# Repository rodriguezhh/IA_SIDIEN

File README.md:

# DIAGNÓSTICO DE ENFERMEDADES EN LA HOJA DEL TOMATE MEDIANTE UN SISTEMA EMBEBIDO USANDO INTELIGENCIA ARTIFICIAL E IMÁGENES.

## Descripción del sistema

Este proyecto tiene como objetivo diseñar e implementar un algoritmo de aprendizaje profundo que permita identificar enfermedades en la hoja de la planta del tomate desplegado en un sistema embebido. El sistema está destinado para servir como herramient a agricultores experimentados como a ingenieros agrónomos, con el objetivo de realizar diagnósticos tempranos y asegurar la salud del cultivo.Además, la implementación de este sistema también puede tener fines educativos, permitiendo el estudio de las enfermedades que afectan a las hojas de tomate y apoyando el seguimiento de los cultivos.

Para llevar a cabo este proyecto, se utilizó una base de datos proporcionada por la comunidad Kaggle. Además, se visitaron diferentes invernaderos para capturar imágenes de hojas sanas y enfermas de los cultivos de tomate. Se emplearon herramientas de software libre y código abierto para cada etapa del proyecto.

Se entrenó una inteligencia artificial de jerarquía simplificada y tres modelos de Transfer Learning utilizando Google Colaboratory.

Finalmente, el modelo resultante fue implementado en dos sistemas embebidos, NVIDIA Jetson Nano de 4GB y Raspberry pi 4B. Se realizó un análisis comparativo de los resultados obtenidos para validar su rendimiento en ambas tarjetas de desarrollo.

## Video sobre el desarrollo del proyecto.
https://youtu.be/ES93pp3hpe4

## Drive del proyecto.
https://drive.google.com/drive/folders/18Io3CUIHZYFtg3d0LMKD3wjqCA_87UzG?usp=sharing

## Manual de Usuario 
### Paso a paso del Hardware
1. Accione el interruptor para encender el dispositivo TOLD2.

2. Si va a hacer uso del porta muestras, accione el interruptor para encender la luz del dispositivo TOLD2.

3. Seleccione la muestra de hoja de la plante del tomate que desea inspeccionar y asegurela con el alfiler en el porta muestras y depositela.

5. Diríjase al apartado ’Paso a paso de la interfaz de usuario’ para proceder con el diagnóstico.

 ### NOTA: 
 En caso de que el dispositivo TOLD2 no encienda, conecte el cargador en el puerto al costado del dispositivo TOLD2. 

### Paso a paso de la Interfaz de usuario 
1. Al iniciar el dispositivo, debe observar la siguiente pantalla.

2. Haga doble click sobre el icono "hacer detección". Acontinuación se debe abrir una interfaz como la siguiente. Asegurese de abrir el software unicamente con dos clicks, de lo contrario se abrirá más de una ventana.

3. Captue la imagen haciendo click en el boton "Tomar foto". 
4. Haga click en el botón "hacer detección". 
5. Finalemte podra observar un diagnóstico de su hoja, además. Si desea realizar otra predicción puede hacer click sobre ”Nueva detección" y repita el proceso cuantas veces desee.

## Contribución
Este proyecto se encuentra en constante evolución, por lo que cualquier contribución será bienvenida. Si deseas contribuir, por favor envía un pull request o contacta al equipo de desarrollo.

## Contacto 
* Camilo Andres Santos Ortiz. camilosantos6584@gmail.com
* Harold Hernando Rodriguez Rodriguez. rodriguezhh03@gmail.com
* Wilmer Andres Guerrero Rangel. andresguerrero1204@gmail.com

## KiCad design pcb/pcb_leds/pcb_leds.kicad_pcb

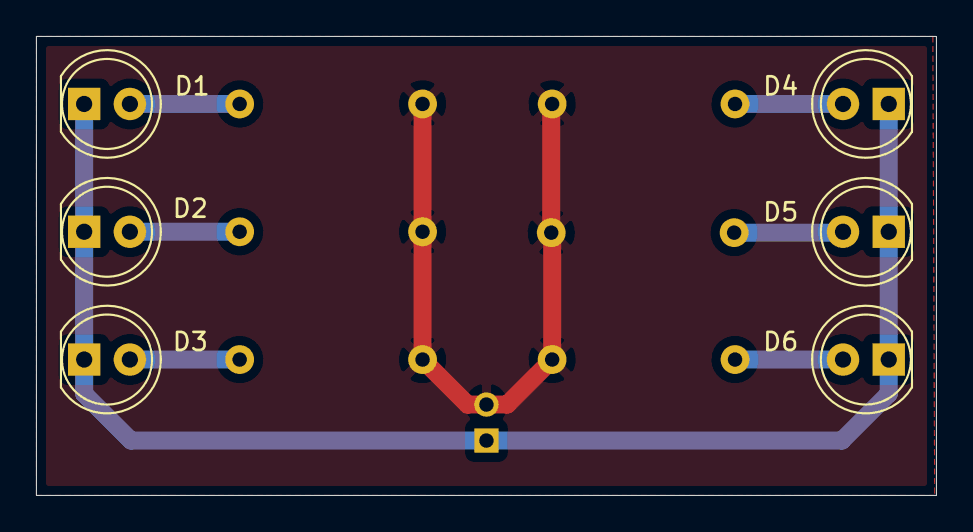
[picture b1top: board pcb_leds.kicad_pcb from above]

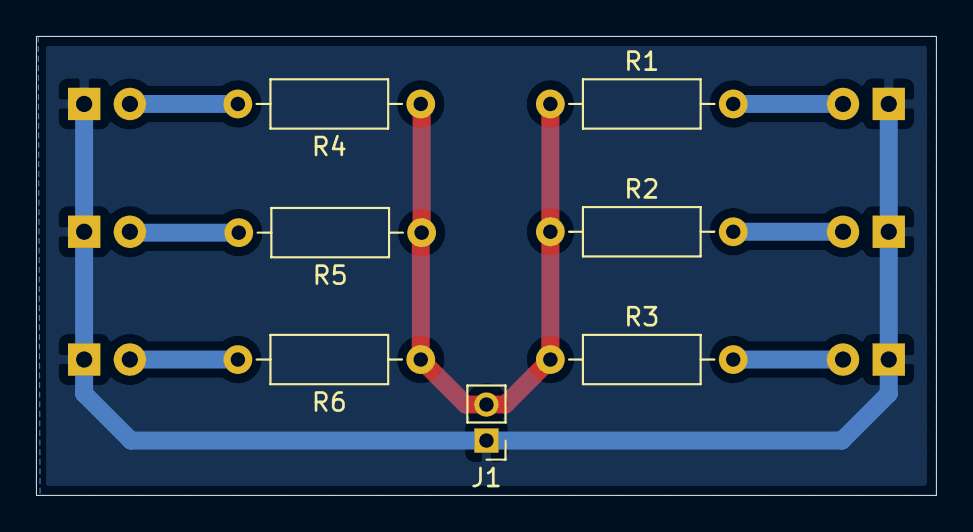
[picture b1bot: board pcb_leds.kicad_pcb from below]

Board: 2 copper layers, 50.0 x 25.5 mm, 13 parts (7 on the bottom side), 8 nets.

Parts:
D1, D2, D3, D4, D5, D6: LED; LED_D5.0mm
J1: Screw_Terminal_01x02; PinHeader_1x02_P2.00mm_Vertical
R1, R2, R3, R4, R5, R6: 160; R_Axial_DIN0207_L6.3mm_D2.5mm_P10.16mm_Horizontal

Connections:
+5V: J1.2, R1.1, R2.1, R3.1, R4.1, R5.1, R6.1
GND: D1.1, D2.1, D3.1, D4.1, D5.1, D6.1, J1.1
unnamed: D1.2, R1.2
unnamed: D2.2, R2.2
unnamed: D3.2, R3.2
unnamed: D4.2, R4.2
unnamed: D5.2, R5.2
unnamed: D6.2, R6.2

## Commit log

2022-08-01 Creado con Colaboratory
2022-08-01 Create
    Ann
2022-12-28 Base inicial para la interfaz, main, gui y archivo qt designer iniciales
2022-12-29 Camara funciona haciendo click en el boton start, aún no se detiene la cámara
2023-01-02 Interfaz funcional para toma de base de datos, permite guardar fotos en una carpeta, nombradas con la fecha y hora del momento
2023-01-08 Se agrega el modelo 3D del cono para el portamuestras junto con el portamuestras
2023-01-20 Cambios con la intefaz para dataset terminada y encapsulado terminado
2023-02-02 Se agregan los archivos STL para impresión 3D, los archivos y planos del diseño de la pcb y los archivos svg para corte laser
2023-03-13 Create Diseño
2023-03-25 Organizacion del GIT
2023-03-25 Remover carpeta de interfaz
2023-03-25 Removiendo PCB
2023-03-25 Remover stl, svg y agregar carpetas
2023-03-25 removiendo archivos fuera de Software
2023-03-25 Remover archivo FCStd del inicio
2023-03-25 Creacion de las carpetas necesarias y ordenamiento
2023-03-25 Se agregaron los archivos FCStd y los archivos stl para impresion
2023-04-03 Creación de las carpetas Dataset y Modelos de IA
2023-04-12 Creado mediante Colaboratory
2023-04-19 Limpieza
2023-04-19 Ajuste de nuevas carpetas
2023-04-19 Ajuste carpeta de pruebas in situ
2023-04-19 Ajuste de archivos en las respectivas carpetas
2023-04-20 Cambios en los archivos de interfaz
2023-04-20 Actualización de archivos .svg
